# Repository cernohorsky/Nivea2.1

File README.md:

# Nivea2.1 - Small CW transciever

Based on: http://home.mlab.cz/Designs/HAM_Constructions/TRX_NIVEAII/DOC/HTML/Radio_NIVEA_II_Navod_V1_0_0A.cs.html

#cw, #transceiver, #ham, #radio

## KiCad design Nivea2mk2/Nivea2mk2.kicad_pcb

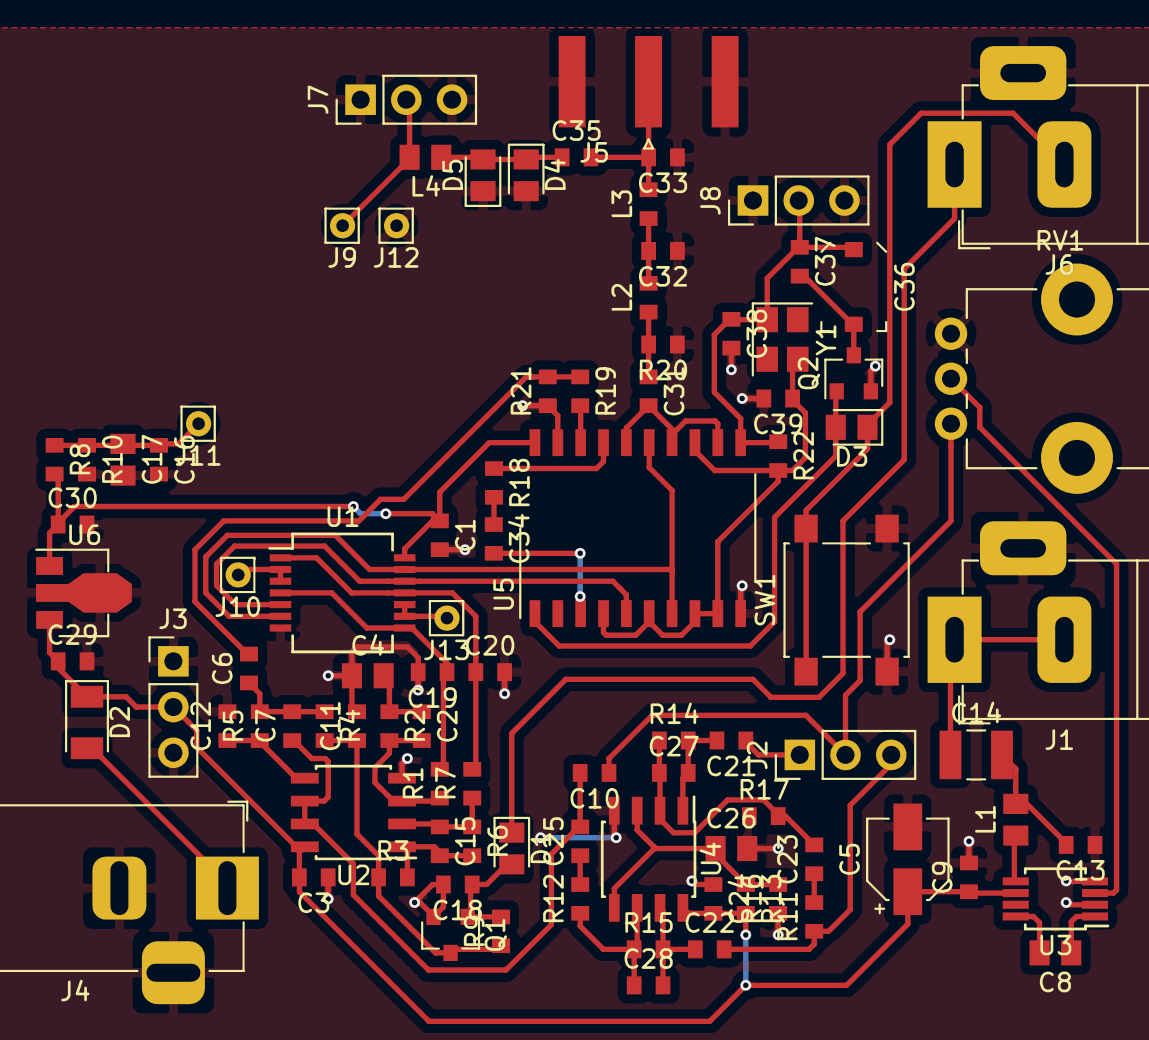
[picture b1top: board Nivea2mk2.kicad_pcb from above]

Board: 2 copper layers, 94 parts (0 on the bottom side), 53 nets.

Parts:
C1, C3, C9, C13, C16, C19, C20, C24, C29, C30, C31, C34: 100n; C_0603_1608Metric
C2, C15: 1n; C_0603_1608Metric
C4, C8, C17, C26: 10u/16V; C_0805_2012Metric
C5: 220uF/16V; CP_Elec_4x5.4
C6, C37, C38, C39: 47p; C_0603_1608Metric
C7: 4n7; C_0603_1608Metric
C10, C21, C22, C25: 10n; C_0603_1608Metric
C11: 47n; C_0603_1608Metric
C12, C33: 330p; C_0603_1608Metric
C14: 47u/16V; C_1210_3225Metric
C18: 220n; C_0603_1608Metric
C23, C27: 15n; C_0603_1608Metric
C28: 560p; C_0603_1608Metric
C32: 820p; C_0603_1608Metric
C35: 27p; C_0603_1608Metric
C36: JR400(8-40p); C_Trimmer_Murata_TZC3
D1, D3, D4, D5: 1N4148; D_0805_2012Metric
D2: 1N5818; D_1206_3216Metric
J1, J6: Audio-Jack-3; Jack_Horizontal
J2, J3, J7, J8: Conn_01x03; PinHeader_1x03_P2.54mm_Vertical
J4: Jack-DC; BarrelJack_Horizontal
J5: SMA; SMA_Amphenol_132289_EdgeMount
J9: M1; Pin_D0.7mm_L6.5mm_W1.8mm_FlatFork
J10: M3; Pin_D0.7mm_L6.5mm_W1.8mm_FlatFork
J11: M4; Pin_D0.7mm_L6.5mm_W1.8mm_FlatFork
J12: M2; Pin_D0.7mm_L6.5mm_W1.8mm_FlatFork
J13: M5; Pin_D0.7mm_L6.5mm_W1.8mm_FlatFork
L1: 330u; C_0805_2012Metric
L2: 220n; C_0603_1608Metric
L3: 470n; C_0603_1608Metric
L4: 4u7; C_0805_2012Metric
Q1: Q_NPN_BEC; SOT-23
Q2: BS170; SOT-23
R1, R7: 100R; R_0603_1608Metric
R2, R6, R9, R19: 10k; R_0603_1608Metric
R3: 2k7; R_0603_1608Metric
R4: 33k; R_0603_1608Metric
R5: 100k; R_0603_1608Metric
R8, R10: 1k5; R_0603_1608Metric
R11, R22: 47k; R_0603_1608Metric
R12: 5k6; R_0603_1608Metric
R13, R16, R20, R21: 3k3; R_0603_1608Metric
R14: 120k; R_0603_1608Metric
R15: 680k; R_0603_1608Metric
R17: 1k8; R_0603_1608Metric
R18: 6k8; R_0603_1608Metric
RV1: 10k/G; Potentiometer_Bourns_PTV09A-1_Single_Vertical
SW1: SW_Push; SW_SPST_B3S-1000
U1: 4066; SSOP-14_5.3x6.2mm_P0.65mm
U2, U4: TL082; SOIC-8_3.9x4.9mm_P1.27mm
U3: LM386; MSOP-8_3x3mm_P0.65mm
U5: 74HC240; SO-20_12.8x7.5mm_P1.27mm
U6: L78L06_SOT89; SOT-89-3
Y1: Crystal_GND24; Crystal_SMD_3225-4Pin_3.2x2.5mm

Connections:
+6V: C1.1, C30.1, R8.2, U1.14, U5.20, U6.1
GND: C1.2, C3.1, C4.1, C5.2, C9.2, C11.2, C12.2, C13.1, C16.2, C17.2, C18.2, C19.2, C20.2, C24.1, C26.2, C29.2, C30.2, C32.1, C33.1, C38.2, C39.2, D4.2, D5.1, J1.3, J3.1, J3.3, J4.2, J4.3, J5.2, J6.3, J7.1, J7.3, J8.1, J8.3, J12.1, Q1.2, Q2.2, R10.2, R16.1, R17.1, R20.1, R21.1, RV1.3, SW1.2, U1.7, U2.4, U3.2, U3.4, U4.4, U5.10, U5.19, U6.2
unnamed: C2.1, C4.2, R2.1
unnamed: C2.2, R1.1, R2.2, U2.3
unnamed: C6.1, C7.2, R4.1, R5.2
unnamed: C8.1, U3.1
unnamed: C8.2, U3.8
unnamed: C10.1, J2.2, RV1.1
unnamed: C7.1, C10.2, C25.2, U2.6, U2.7
unnamed: C11.1, Q1.3, R3.1, R4.2, R9.1
unnamed: C12.1, R5.1, U2.5
unnamed: C13.2, C14.2, L1.2
unnamed: C14.1, J1.1, J1.2
unnamed: C15.1, R6.1, R7.1, U2.2
unnamed: C15.2, R3.2, R6.2, U2.1
unnamed: C16.1, C17.1, J11.1, R8.1, R10.1
unnamed: C18.1, D1.2, Q1.1, R9.2
unnamed: C19.1, R1.2, U1.4, U1.8
unnamed: C20.1, R7.2, U1.1, U1.11
unnamed: C21.1, J2.1
unnamed: C21.2, C27.2, R14.2, U4.1
unnamed: C22.1, C28.2, R15.2, U4.7
unnamed: C22.2, J2.3, R11.1
unnamed: C23.1, R11.2
unnamed: C23.2, C27.1, R14.1, R17.2, U4.2
unnamed: C25.1, R12.2
unnamed: C26.1, R13.1, R16.2, U4.3, U4.5
unnamed: C28.1, R12.1, R15.1, U4.6
unnamed: C31.1, L2.1, R20.2
unnamed: C31.2, U5.12, U5.14, U5.16
unnamed: C32.2, L2.2, L3.1
unnamed: C33.2, C35.2, J5.1, L3.2
unnamed: C34.1, R18.2
unnamed: C34.2, U5.3
unnamed: C35.1, D4.1, D5.2, L4.1
unnamed: C36.1, C37.1, C38.1, J8.2, R22.1, U5.11, Y1.1
unnamed: C36.2, C37.2, Q2.3
unnamed: C39.1, R22.2, U5.4, U5.6, U5.8, U5.9, U5.13, Y1.3
unnamed: D2.2, J4.1
unnamed: D3.1, J6.2, SW1.1
unnamed: D3.2, Q2.1, U5.1
unnamed: J10.1, U1.2, U1.3
unnamed: J13.1, U1.9, U1.10
unnamed: L1.1, U3.5
unnamed: R18.1, U5.17
unnamed: R19.2, U5.18
unnamed: RV1.2, U3.3
PTT: D1.1, J6.1
RX: J7.2, J9.1, L4.2
SIDETONE: C6.2, R19.1, R21.2
VCC: C3.2, C5.1, C9.1, C24.2, C29.1, D2.1, J3.2, R13.2, U2.8, U3.6, U4.8, U6.3
VFO_0: U1.6, U1.13, U5.7, U5.15
VFO_90: U1.5, U1.12, U5.5

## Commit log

2020-01-09 First concept
2020-01-10 Added edge cuts and picture
2020-01-13 Added schematic pictures
